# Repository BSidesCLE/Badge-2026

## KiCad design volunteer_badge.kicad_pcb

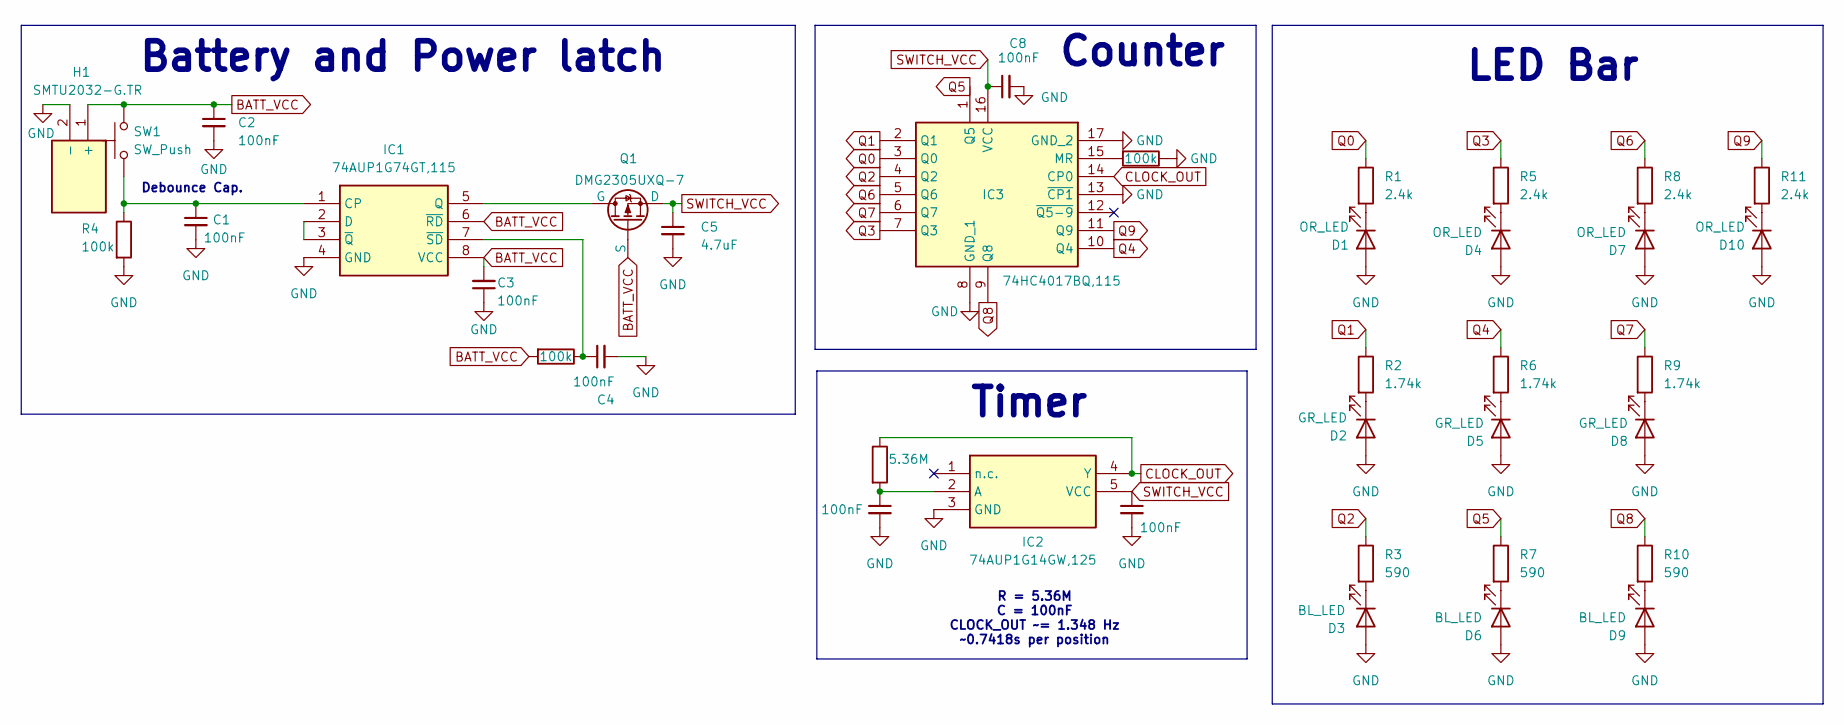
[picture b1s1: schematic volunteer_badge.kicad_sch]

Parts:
C1, C2, C3, C4, C6, C7, C8: 100nF; C_0402_1005Metric
C5: 4.7uF; C_0402_1005Metric
D1, D4, D7, D10: OR_LED; LED_QBLP601_0603
D2, D5, D8: GR_LED; LED_QBLP601_0603
D3, D6, D9: BL_LED; LED_QBLP601_0603
H1: SMTU2032-G.TR; BatteryHolder_Renata_SMTU2032-LF_1x2032; Manufacturer_Part_Number SMTU2032-G.TR; Mouser Part Number 614-SMTU2032-G.TR
IC1: 74AUP1G74GT,115; 74AVC9112GTX; Manufacturer_Part_Number 74AUP1G74GT,115; Mouser Part Number 771-AUP1GGT115
IC2: 74AUP1G14GW,125; SOT65P212X110-5N; Manufacturer_Part_Number 74AUP1G14GW,125; Mouser Part Number 771-AUP1G14GW125
IC3: 74HC4017BQ,115; 74HC4017BQ115; Manufacturer_Part_Number 74HC4017BQ,115; Mouser Part Number 771-HC4017BQ115
Q1: DMG2305UXQ-7; SOT-23
R1, R5, R8, R11: 2.4k; R_0402_1005Metric
R2, R6, R9: 1.74k; R_0402_1005Metric
R3, R7, R10: 590; R_0402_1005Metric
R4, R12, R14: 100k; R_0402_1005Metric
R13: 5.36M; R_0402_1005Metric
SW1: SW_Push; SW_Mitsumi_R-668003

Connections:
BATT_VCC: C2.1, C3.2, H1.1 (+), IC1.6 (~RD), IC1.8 (VCC), Q1.2 (S), R12.2, SW1.2
CLOCK_OUT: IC2.4 (Y), IC3.14 (CP0), R13.1
GND: C1.2, C2.2, C3.1, C4.2, C5.2, C6.2, C7.2, C8.2, D1.2 (K), D2.2 (K), D3.2 (K), D4.2 (K), D5.2 (K), D6.2 (K), D7.2 (K), D8.2 (K), D9.2 (K), D10.2 (K), H1.2 (-), IC1.4 (GND), IC2.3 (GND), IC3.8 (GND_1), IC3.13 (~CP1), IC3.17 (GND_2), R4.2, R14.1
unnamed: D1.1 (A), R1.2
unnamed: D2.1 (A), R2.2
unnamed: D3.1 (A), R3.2
unnamed: D4.1 (A), R5.2
unnamed: D5.1 (A), R6.2
unnamed: D6.1 (A), R7.2
unnamed: D7.1 (A), R8.2
unnamed: D8.1 (A), R9.2
unnamed: D9.1 (A), R10.2
unnamed: D10.1 (A), R11.2
unnamed: C1.1, IC1.1 (CP), R4.1, SW1.1
unnamed: IC1.2 (D), IC1.3 (~Q)
unnamed: IC1.5 (Q), Q1.1 (G)
unnamed: C4.1, IC1.7 (~SD), R12.1
unnamed: C6.1, IC2.2 (A), R13.2
unnamed: IC3.15 (MR), R14.2
Q0: IC3.3 (Q0), R1.1
Q1: IC3.2 (Q1), R2.1
Q2: IC3.4 (Q2), R3.1
Q3: IC3.7 (Q3), R5.1
Q4: IC3.10 (Q4), R6.1
Q5: IC3.1 (Q5), R7.1
Q6: IC3.5 (Q6), R8.1
Q7: IC3.6 (Q7), R9.1
Q8: IC3.9 (Q8), R10.1
Q9: IC3.11 (Q9), R11.1
SWITCH_VCC: C5.1, C7.1, C8.1, IC2.5 (VCC), IC3.16 (VCC), Q1.3 (D)

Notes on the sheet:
Timer
Battery and Power latch
R = 5.36M C = 100nF CLOCK_OUT ~= 1.348 Hz ~0.7418s per position
Counter
LED Bar
Debounce Cap.

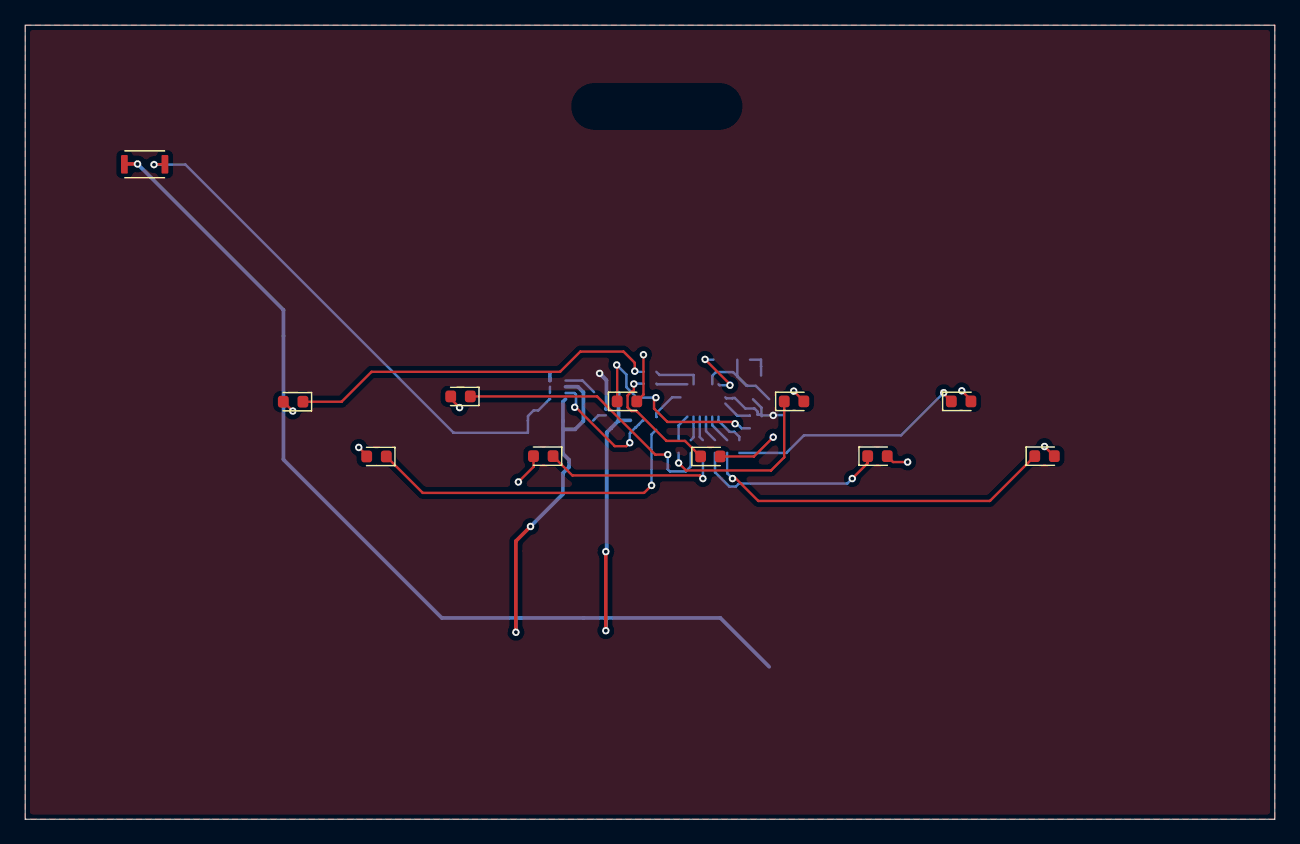
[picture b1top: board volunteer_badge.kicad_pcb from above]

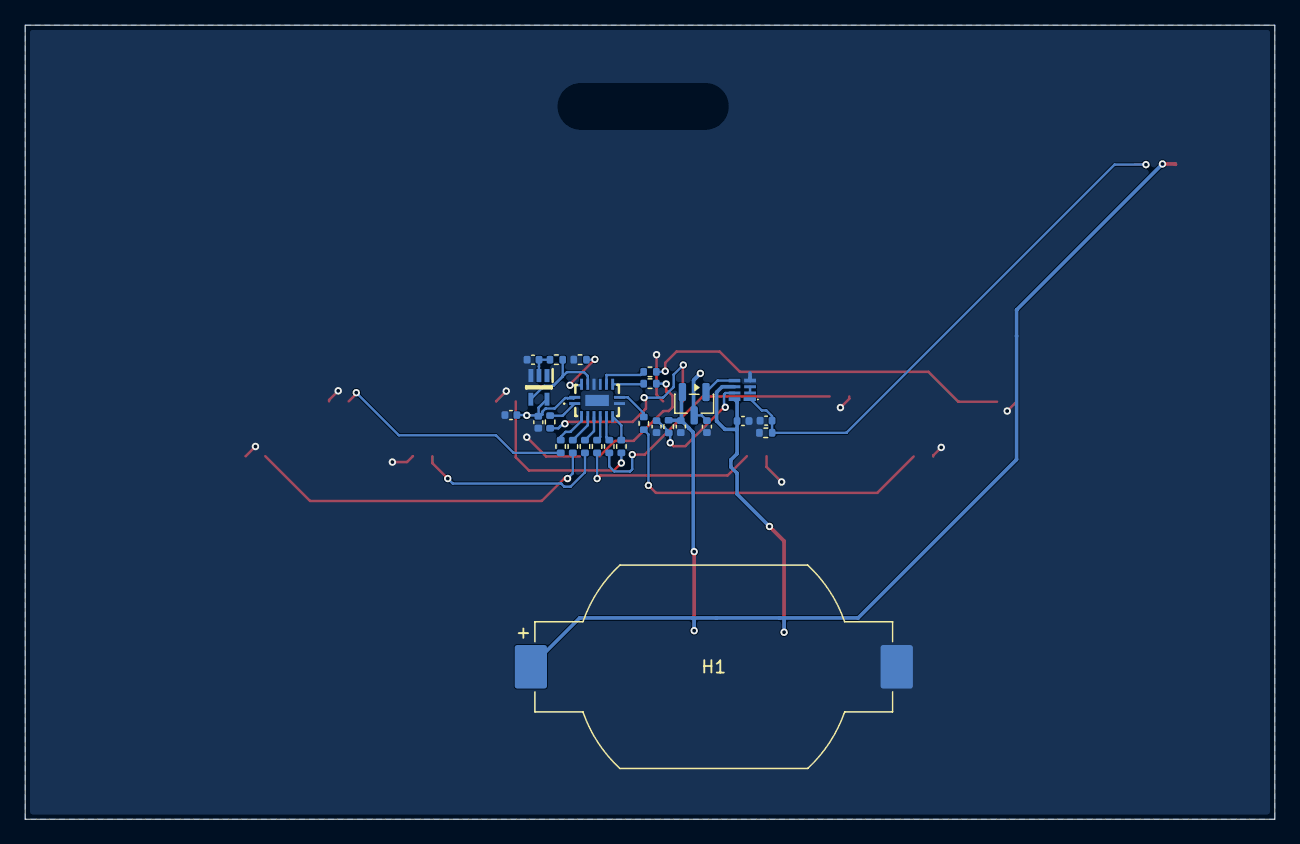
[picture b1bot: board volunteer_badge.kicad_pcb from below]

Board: 2 copper layers, 100.4 x 63.8 mm, 39 parts (27 on the bottom side), 30 nets.

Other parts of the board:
H?: Lanyard_Slot_13x3mm_NPTH
